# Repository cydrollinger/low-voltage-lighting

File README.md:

<a href="https://elec-real.com/case-studies/low-voltage-lighting/"></img></a>
>Electronic Realization L.L.C.								   
>Design: Hardware design of 4 LEDs		   
>Engineer: Cy Drollinger								   
>Date: 3/16												           
>Email: cy@elec-real.com
>Website: https://elec-real.com								   
>Address: 2023 Stadium Dr Suite 2B #210 Bozeman, MT 59715				   
>Phone: 406-539-8117	

**NOTE:**
 This design has been tested and functions as specified. The design is provided gratis, so, please 
 think critically while utilizing and or redesigning. Open electronic circuitry can be dangerous due 
 to easily shorting circuits which can generate immediate and intense heat resulting in fire. Conversation is
 welcome to improve this design and repository, but, be advised ER is a professional design house and
 monetary compensation is required for additional work toward this design enabling your success.			   

**PURPOSE:**
Four power LEDs are driven by a timer block from a low voltage supply. The timer block switches the LEDs on
and off the input voltage designed at 3.3v. The brightness of the LEDs is managed by a varying a resistor that
controls the duty cycle, 0-100%, of a 100Hz square wave.
  
>**File Arcitecture with a terse description**

* FOLDERS:
	* docs		: datasheets charging IC and battery holder
	* hardware	: eagle cadsoft(v7.7) hardware design files 	
		* library		: eagle part files 
		* manufacturing	: files required to produce the design
			* bom	: files created to order the parts	
			* gerber	: files generated to manufacture the board
			* <a href="https://oshpark.com/shared_projects/x1jqUElK"></img></a>
	
	* readme.md	: this file

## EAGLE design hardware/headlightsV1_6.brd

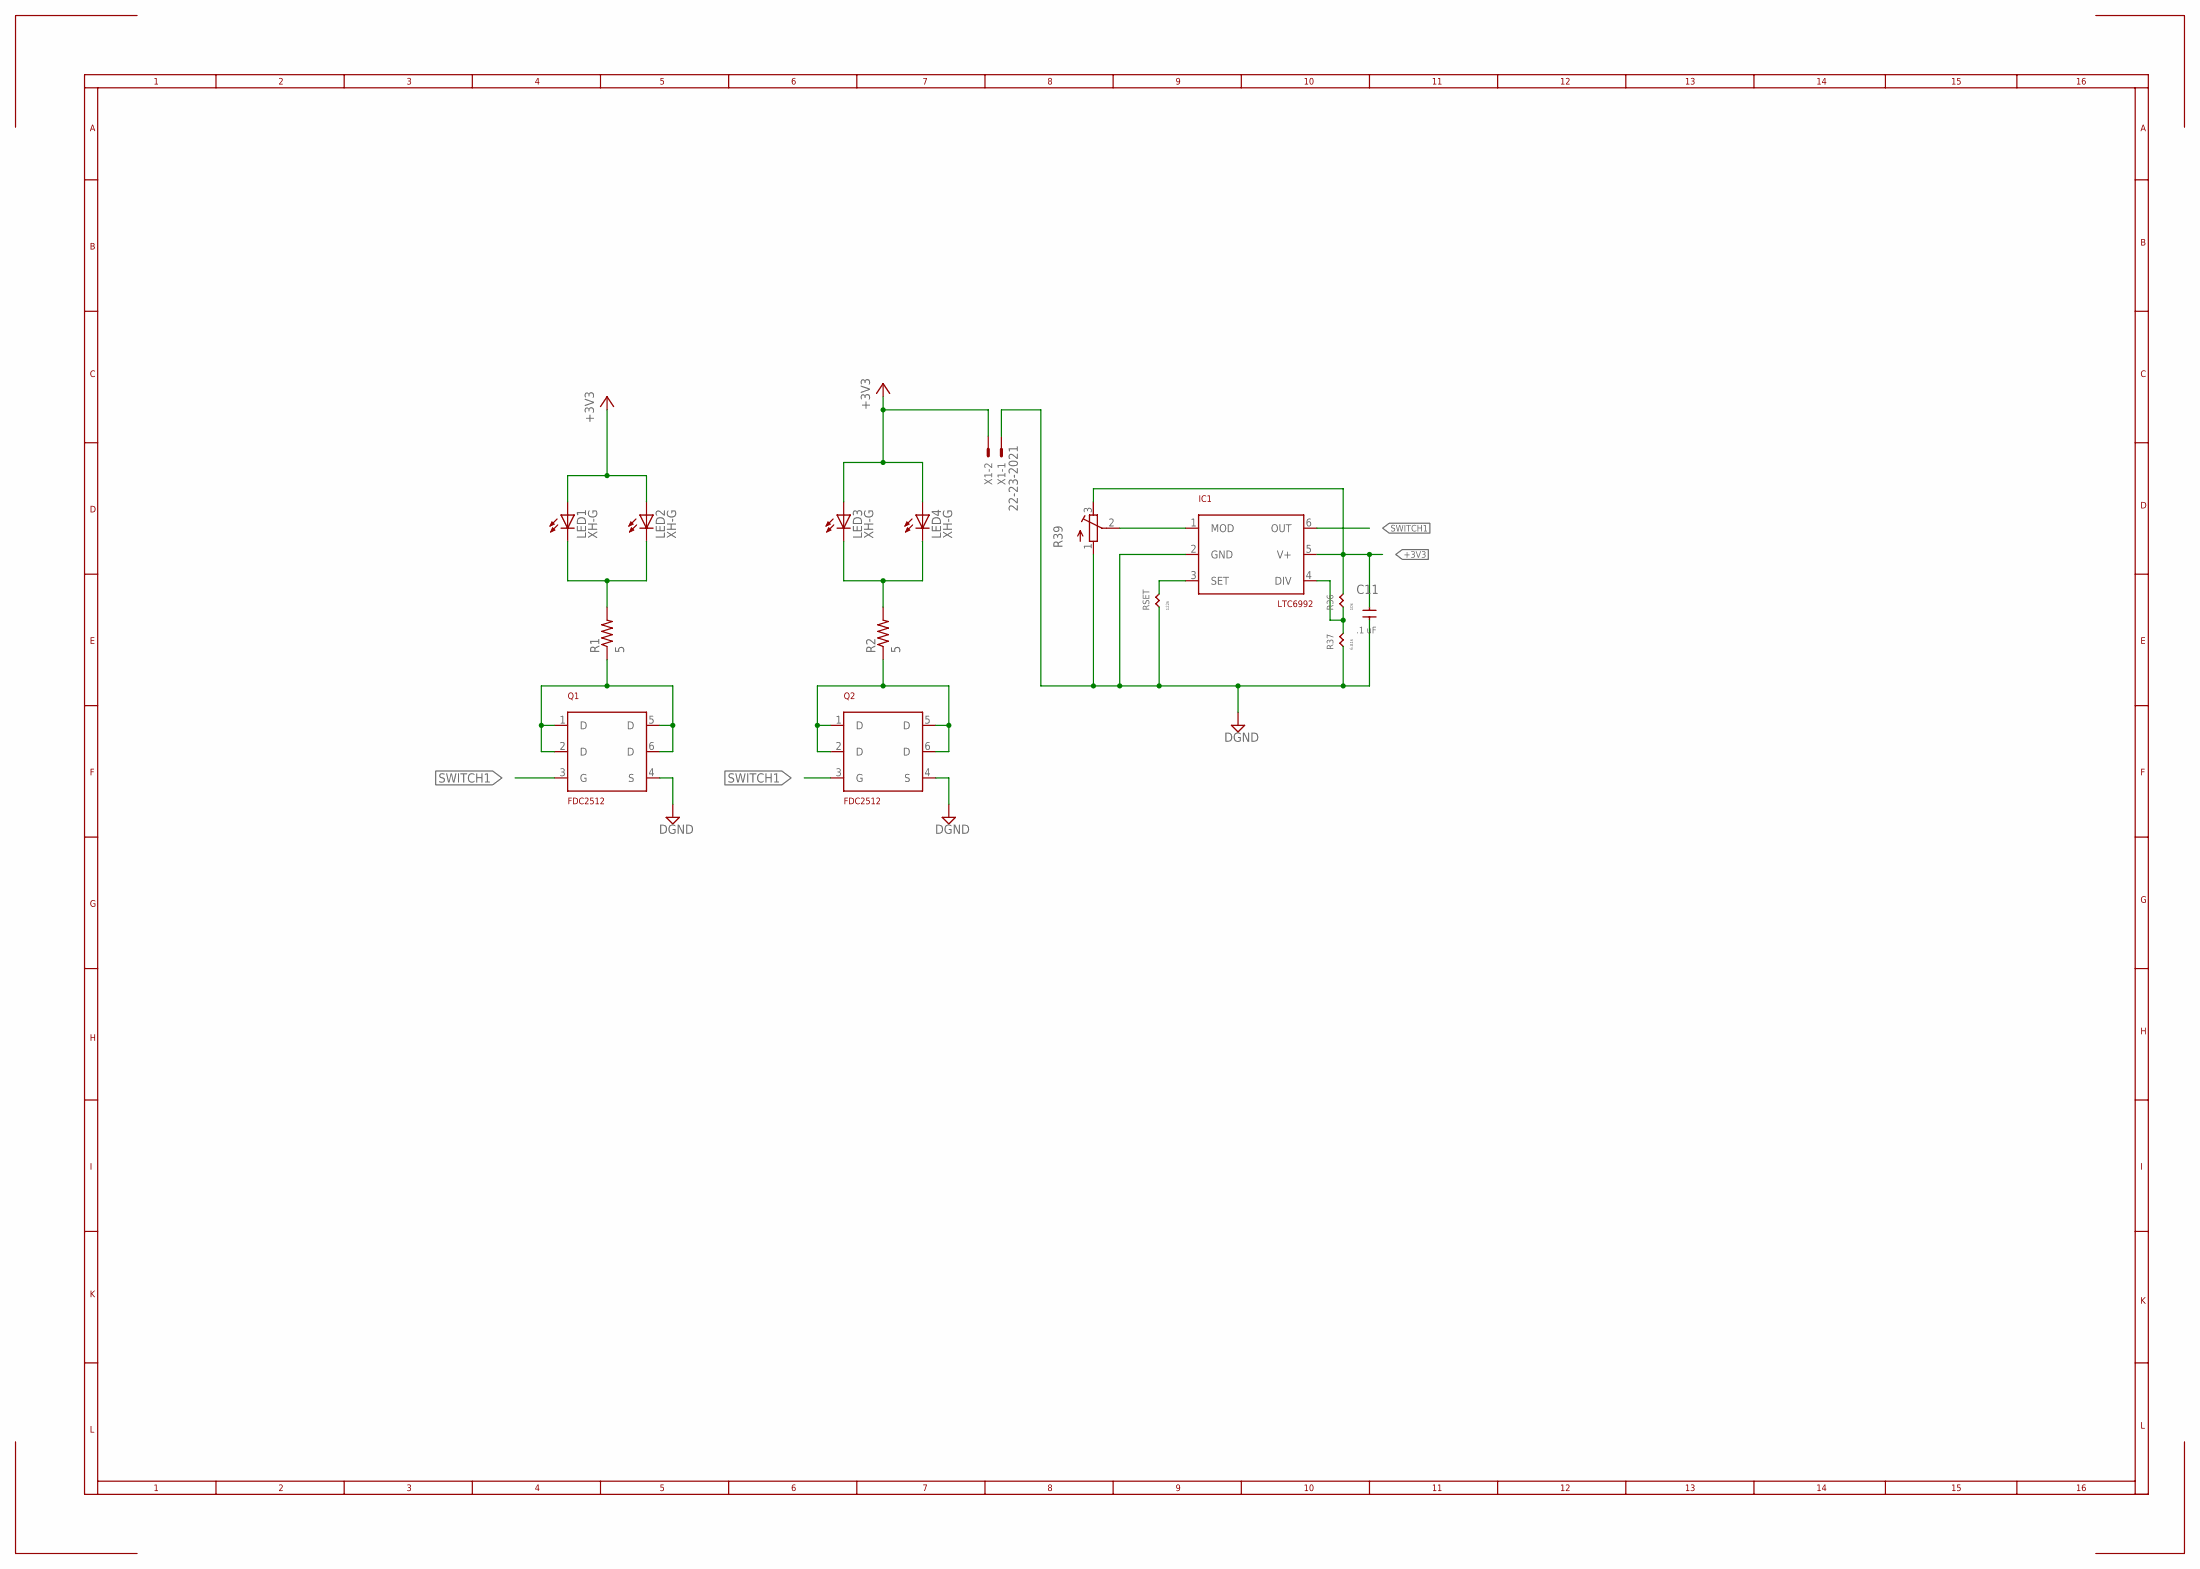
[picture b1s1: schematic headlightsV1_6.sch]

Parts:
C11: .1 uF; C0402
IC1: LTC6992; TSOT-23-6
LED1, LED2, LED3, LED4: XH-G
Q1, Q2: FDC2512; SSOT6
R1, R2: 5; R0805
R36: 10k; R0402
R37: 6.81k; R0402
R39: R-TRIMM3304W; RTRIM3304W
RSET: 122k; R0402
X1: 22-23-2021

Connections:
+3V3: C11.2, IC1.5 (V+), LED1.2 (A), LED2.2 (A), LED3.2 (A), LED4.2 (A), R36.2, R39.3 (A), X1.2
DGND: C11.1, IC1.2 (GND), Q1.4 (S), Q2.4 (S), R37.1, R39.1 (E), RSET.1, X1.1
unnamed: Q1.1 (D), Q1.2 (D), Q1.5 (D), Q1.6 (D), R1.1
unnamed: Q2.1 (D), Q2.2 (D), Q2.5 (D), Q2.6 (D), R2.1
unnamed: LED3.1 (C), LED4.1 (C), R2.2
unnamed: IC1.4 (DIV), R36.1, R37.2
unnamed: IC1.3 (SET), RSET.2
unnamed: IC1.1 (MOD), R39.2 (S)
unnamed: LED1.1 (C), LED2.1 (C), R1.2
SWITCH1: IC1.6 (OUT), Q1.3 (G), Q2.3 (G)

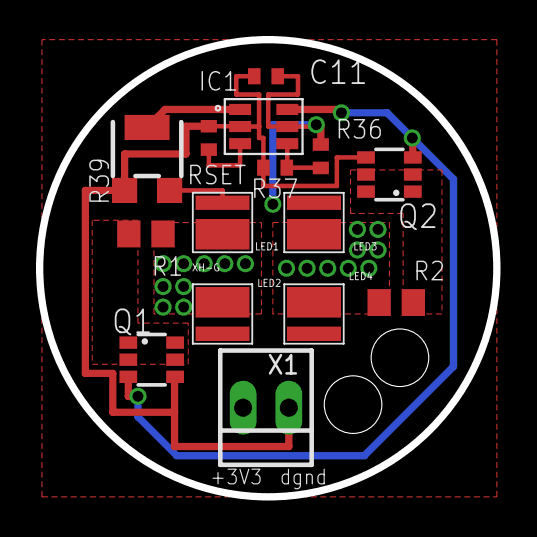
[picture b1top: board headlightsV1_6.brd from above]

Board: 2 copper layers, 25.4 x 25.4 mm, 15 parts (0 on the bottom side), 10 nets.

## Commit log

2019-04-19 first commit 4/19/19
2019-04-26 first commit 4/26/19
2019-04-27 first commit 4/27/19
2019-04-30 first commit 4/30/19
